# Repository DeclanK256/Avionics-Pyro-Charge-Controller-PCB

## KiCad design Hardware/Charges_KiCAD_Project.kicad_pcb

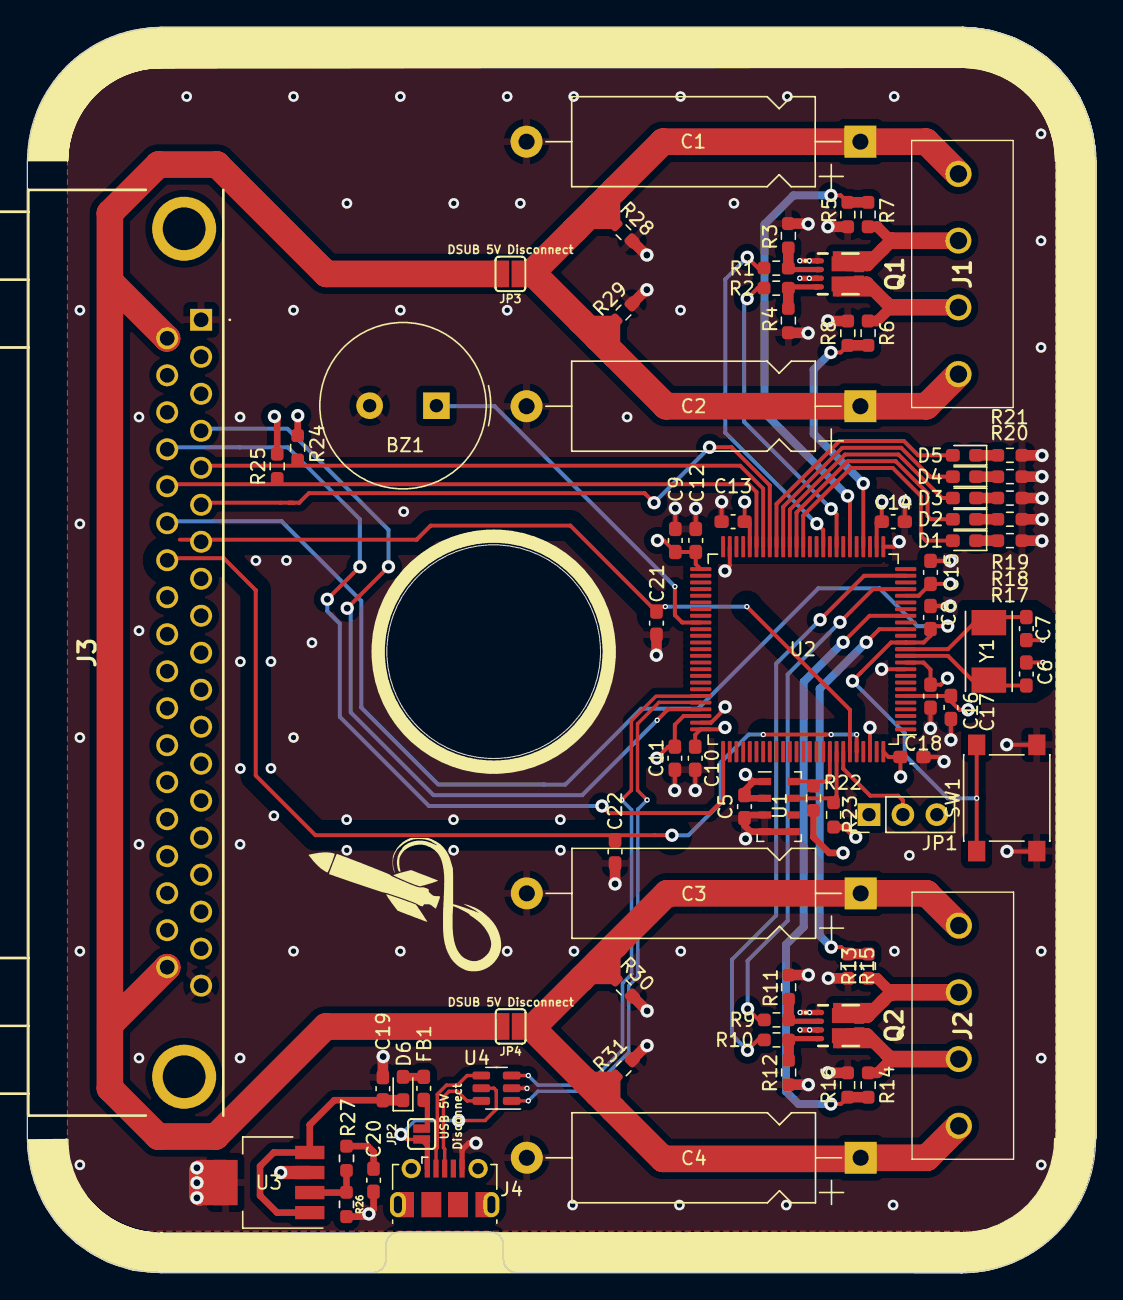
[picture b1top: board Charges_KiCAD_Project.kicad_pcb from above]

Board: 4 copper layers, 80.0 x 93.2 mm, 77 parts (0 on the bottom side), 54 nets.

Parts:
BZ1: TP124005-2; Buzzer_TDK_PS1240P02BT_D12.2mm_H6.5mm
C1, C2, C3, C4: 1500uF; CP_Axial_L18.0mm_D6.5mm_P25.00mm_Horizontal
C5, C8, C10, C11, C12, C13, C14, C15, C16, C17, C18, C21, C22: 100nF; C_0603_1608Metric_Pad1.08x0.95mm_HandSolder
C6, C7: 30pF; C_0603_1608Metric_Pad1.08x0.95mm_HandSolder
C9, C20: 1uF; C_0603_1608Metric_Pad1.08x0.95mm_HandSolder
C19: 0.1uF; C_0603_1608Metric_Pad1.08x0.95mm_HandSolder
D1, D3, D5: Red; LED_0603_1608Metric_Pad1.05x0.95mm_HandSolder
D2, D4: Grn; LED_0603_1608Metric_Pad1.05x0.95mm_HandSolder
D6: D_Schottky_Small; D_0603_1608Metric_Pad1.05x0.95mm_HandSolder
FB1: Ferrite_Bead_Small; C_0603_1608Metric_Pad1.08x0.95mm_HandSolder
J1, J2: Terminal Block; TB00250004BE
J3: DB37_Male_MountingHoles; L717SDC37P1ACH4F
J4: 10118192-0001LF; USB_Micro-B_Molex-105017-0001
JP1: Debug Jumper; PinHeader_1x03_P2.54mm_Vertical
JP2: USB 5V Disconnect; SMT-JUMPER_2_NO_SILK
JP3, JP4: DSUB 5V Disconnect; SMT-JUMPER_2_NO_SILK
Q1, Q2: SI7232DN-T1-GE3; SI7232DNT1GE3
R1, R2, R9, R10: 1k; R_0603_1608Metric_Pad0.98x0.95mm_HandSolder
R3, R4, R11, R12, R28, R29, R30, R31: 10k; R_0603_1608Metric_Pad0.98x0.95mm_HandSolder
R5, R6, R13, R14: 100k; R_0603_1608Metric_Pad0.98x0.95mm_HandSolder
R7, R8, R15, R16: 27k; R_0603_1608Metric_Pad0.98x0.95mm_HandSolder
R17, R18, R19, R20, R21: 820; R_0603_1608Metric_Pad0.98x0.95mm_HandSolder
R22, R23, R24, R25: 4.7k; R_0603_1608Metric_Pad0.98x0.95mm_HandSolder
R26: 390; R_0603_1608Metric_Pad0.98x0.95mm_HandSolder
R27: 240; R_0603_1608Metric_Pad0.98x0.95mm_HandSolder
SW1: MCU Reset; SW_SPST_PTS645
U1: MS5607-02BA; LGA-8_3x5mm_P1.25mm
U2: STM32L562VET6Q; LQFP-100_14x14mm_P0.5mm
U3: LP38692MPX-ADJ; SOT-223-5
U4: USBLC6-2SC6; SOT-23-6
Y1: 32MHz; XTAL_ABM7-32.000MHZ-D2Y-T

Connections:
+3V3: C5.2, C9.1, C10.1, C11.1, C12.1, C13.1, C14.1, C15.1, C16.1, C17.1, C18.1, J3.2, J3.18, JP1.3 (B), R22.2, R23.2, R24.2, R25.2, U1.1 (VDD), U1.2 (PS), U2.6 (VBAT), U2.11 (VDD), U2.21 (VDDA), U2.27 (VDD), U2.46 (VDDSMPS), U2.51 (VDD), U2.73 (VDDUSB), U2.75 (VDD), U2.100 (VDD), U3.3 (VOUT)
+5V: C1.1, C2.1, C3.1, C4.1, J1.1, J1.4, J2.1, J2.4, JP3.1 (A), JP4.1 (A), R28.1, R29.1, R30.1, R31.1
/37 Pin DSUB/Alert_Active: J3.6, U2.43 (PE15)
/37 Pin DSUB/Alert_scl: J3.5, R24.1, U2.44 (PB10)
/37 Pin DSUB/Alert_sda: J3.24, R25.1, U2.45 (PB11)
/37 Pin DSUB/DSUB-5V: J3.20, J3.37, JP3.2 (B), JP4.2 (B)
/37 Pin DSUB/Fire: C21.2, J3.7, U2.95 (PB8)
/37 Pin DSUB/Fire_redundant: C22.2, J3.26, U2.96 (PB9)
/37 Pin DSUB/NRST: C8.1, J3.25, SW1.1, U2.14 (NRST)
/37 Pin DSUB/SWCLK: J3.23, U2.76 (PA14)
/37 Pin DSUB/SWDIO: J3.4, U2.72 (PA13)
/Barometer_MS5607/SCLK: R22.1, U1.8 (SCLK), U2.92 (PB6)
/Barometer_MS5607/SDI_SDA: R23.1, U1.7 (SDI/SDA), U2.93 (PB7)
/Fire_A: R1.1, U2.35 (PE7)
/Fire_B: R2.1, U2.33 (PB1)
/Fire_C: R9.1, U2.22 (PA0)
/Fire_D: R10.1, U2.24 (PA2)
/Igniter A: J1.2, Q1.7 (D1_1), Q1.8 (D1_2), Q1.9 (D1_3), Q1.10 (D1_4), Q1.11 (D1_5), Q1.15 (D1_6), R5.1
/Igniter B: J1.3, Q1.5 (D2_1), Q1.6 (D2_2), Q1.12 (D2_3), Q1.13 (D2_4), Q1.14 (D2_5), Q1.16 (D2_6), R6.1
/Igniter C: J2.2, Q2.7 (D1_1), Q2.8 (D1_2), Q2.9 (D1_3), Q2.10 (D1_4), Q2.11 (D1_5), Q2.15 (D1_6), R13.1
/Igniter D: J2.3, Q2.5 (D2_1), Q2.6 (D2_2), Q2.12 (D2_3), Q2.13 (D2_4), Q2.14 (D2_5), Q2.16 (D2_6), R14.1
/MCU L562VET6Q/Buzzer: BZ1.1, U2.59 (PD12)
/MCU L562VET6Q/USB_D+: U2.71 (PA12), U4.1 (IO1)
/MCU L562VET6Q/USB_D-: U2.70 (PA11), U4.3 (IO2)
/Sense_A: R5.2, R7.1, U2.31 (PA7)
/Sense_B: R6.2, R8.1, U2.29 (PA5)
/Sense_C: R13.2, R15.1, U2.16 (PC1)
/Sense_D: R14.2, R16.1, U2.18 (PC3)
/USB Connector and ESD/USB_5V: J4.1, JP2.1 (A), U4.5 (VBUS)
/USB Connector and ESD/USB_CONN_D+: J4.3, U4.6 (IO1)
/USB Connector and ESD/USB_CONN_D-: J4.2, U4.4 (IO2)
GND: BZ1.2, C1.2, C2.2, C3.2, C4.2, C5.1, C6.2, C7.2, C8.2, C9.2, C10.2, C11.2, C12.2, C13.2, C14.2, C15.2, C16.2, C17.2, C18.2, C19.2, C20.2, C21.1, C22.1, J3.1, J3.19, J4.5, JP1.1 (A), Q1.1 (S1), Q1.3 (S2), Q2.1 (S1), Q2.3 (S2), R3.2, R4.2, R7.2, R8.2, R11.2, R12.2, R15.2, R16.2, R17.1, R18.1, R19.1, R20.1, R21.1, R26.2, R28.2, R29.2, R30.2, R31.2, SW1.2, U1.3 (GND), U1.4 (CSB), U1.5 (CSB), U2.10 (VSS), U2.26 (VSS), U2.49 (VSS), U2.74 (VSS), U2.98 (VSS), U3.5 (GND), U4.2 (GND)
unnamed: C6.1, U2.12 (PH0), Y1.1
unnamed: C7.1, U2.13 (PH1), Y1.2
unnamed: C19.1, D6.1 (K), U3.1 (EN), U3.4 (VIN)
unnamed: C20.1, R27.1
unnamed: D1.1 (K), R17.2
unnamed: D1.2 (A), U2.38 (PE10)
unnamed: D2.1 (K), R18.2
unnamed: D2.2 (A), U2.39 (PE11)
unnamed: D3.1 (K), R19.2
unnamed: D3.2 (A), U2.40 (PE12)
unnamed: D4.1 (K), R20.2
unnamed: D4.2 (A), U2.41 (PE13)
unnamed: D5.1 (K), R21.2
unnamed: D5.2 (A), U2.42 (PE14)
unnamed: D6.2 (A), FB1.1
unnamed: FB1.2, JP2.2 (B)
unnamed: JP1.2 (C), U2.94 (PH3)
unnamed: Q1.2 (G1), R1.2, R3.1
unnamed: Q1.4 (G2), R2.2, R4.1
unnamed: Q2.2 (G1), R9.2, R11.1
unnamed: Q2.4 (G2), R10.2, R12.1
unnamed: R26.1, R27.2, U3.2 (ADJ)

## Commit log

2022-02-19 Moved center hole to the left by 2 mm.
    someone made an opsie and forgot that the dsub was WIDE. moved the center hole and a few traces over. remade two traces to eliminate right angles.
